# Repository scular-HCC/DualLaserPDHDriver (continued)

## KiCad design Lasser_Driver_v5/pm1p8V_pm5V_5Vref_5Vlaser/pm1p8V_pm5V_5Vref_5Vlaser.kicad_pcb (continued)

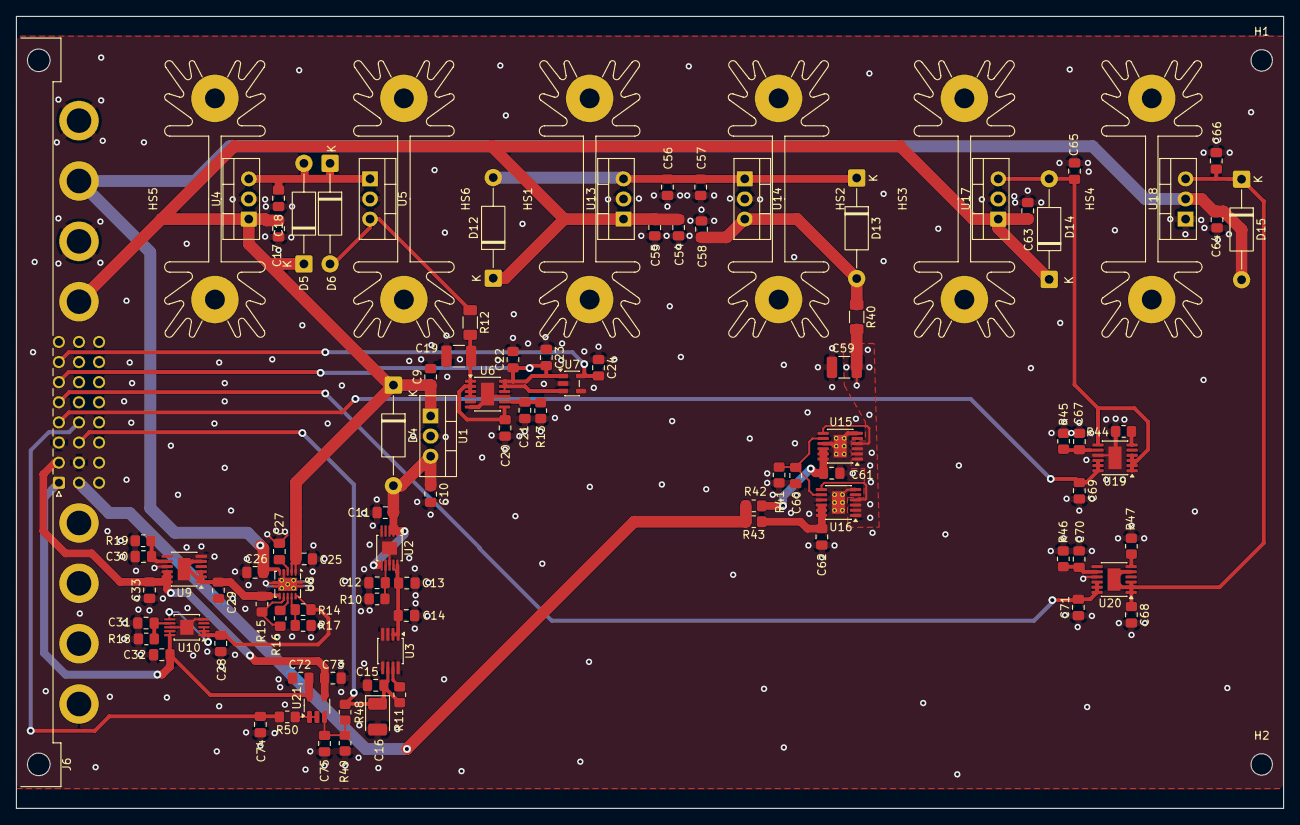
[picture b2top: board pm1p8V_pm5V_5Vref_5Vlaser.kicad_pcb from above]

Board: 2 copper layers, 160.0 x 100.0 mm, 103 parts (0 on the bottom side), 42 nets.

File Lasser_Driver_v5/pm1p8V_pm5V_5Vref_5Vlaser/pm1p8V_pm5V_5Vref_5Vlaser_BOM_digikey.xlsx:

Quantity | Manufacturer Part Number | Manufacturer | Customer Reference | Description
11 | CL21B104KBCNNNC | Samsung Electro-Mechanics | C9, C10, C14, C17, C18, C27, C55, C58, C72, C73, C74 | 100nF
12 | CL21B475KAFNNNE | Samsung Electro-Mechanics | C11, C12, C13, C20, C21, C30, C31, C54, C56, C60, C67, C70 | 4.7uF X7R
15 | C0805C106K3PACTU | KEMET | C15, C22, C25, C26, C28, C29, C32, C33, C61, C62, C65, C66, C68, C69, C71 | 10uF
1 | T520B106M016ATE100 | KEMET | C16 | 10uF 16V Polymer
1 | TMK325ABJ476MM-P | Taiyo Yuden | C19 | 47uF RC
3 | C0805C105K5RACTU | KEMET | C23, C24, C75 | 1uF
3 | CL21B334KBFNNNE | Samsung Electro-Mechanics | C57, C63, C64 | 0.33uF
1 | 1210YD107MAT2A | KYOCERA AVX | C59 | 100uF
7 | 1N4007RLG | onsemi | D4, D5, D6, D12, D13, D14, D15 | 1N4007
1 | 374144-E | TE Connectivity | J6 | DIN41612_M_3x8+8_Power_Male
1 | ERA-6AEB6042V | Panasonic Industry | R10 | 60.4k 0.1%
1 | CRCW08051K00FKEA | Vishay Dale | R17 | 1k
1 | RC1206FR-074R7L | YAGEO | R12 | 4.7R
1 | ERA-6AEB3322V | Panasonic Industry | R13 | 33.2k 0.1%
1 | ERA-6AEB1272V | Panasonic Industry | R14 | 12.7k 0.1%
2 | ERA-6AEB1433V | Panasonic Industry | R18, R19 | 143k 0.1%
1 | RC1206FR-071RL | YAGEO | R40 | 1R RC
2 | ERA-6AEB4992V | Panasonic Industry | R45, R46 | 49.9k 0.1%
1 | RC0805FR-0716KL | YAGEO | R47 | 16k
3 | MC7808CTG | onsemi | U1, U14, U17 | MC7808CTG
2 | LT3042EMSE#PBF | Analog Devices Inc. | U2, U10 | LT3042EMSE +5.5V
1 | LTC6655BHMS8-5#PBF | Analog Devices Inc. | U3 | LTC6655BHMS8-5#PBF
2 | MC7812CTG | onsemi | U4, U13 | MC7812CTG
1 | MC7805CTG | onsemi | U5 | MC7805CTG
4 | LT3045EMSE#PBF | Analog Devices Inc. | U6, U15, U16, U19 | LT3045EMSE 5V
1 | LP5907MFX-1.8/NOPB | Texas Instruments | U7 | LP5907MFX-1.8
1 | TPS7A3901DSCR | Texas Instruments | U8 | TPS7A3901DSCR
2 | LT3094EMSE#PBF | Analog Devices Inc. | U9, U20 | LT3094EMSE -14.3V
1 | MC7906CTG | onsemi | U18 | MC7906CTG
1 | OPA192IDBVR | Texas Instruments | U21 | OPA192IDBVR
1 | RC0805JR-070RL | YAGEO | R11 | 0R
1 | ERA-6AEB1373V | Panasonic Industry | R15 | 137k 0.1%
3 | ERA-6AEB103V | Panasonic Industry | R16, R48, R49 | 10k 0.1%
1 | ERA-6AEB2492V | Panasonic Industry | R41 | 24.9k 0.1%
1 | RC0805FR-07604RL | YAGEO | R44 | 604
1 | ERJ-6ENF49R9V | Panasonic Industry | R50 | 49.9R
6 | 531102B02500G | Boyd | HS1, HS2, HS3, HS4, HS5, HS6 | Heatsink TO-220
6 | 4880G | Boyd | U4, U5, U13, U14, U17, U18 iso kits | TO-220 mount kit
2 | ERJ-6BWFR020V | Panasonic Industry | R42, R43 | 20m 1%

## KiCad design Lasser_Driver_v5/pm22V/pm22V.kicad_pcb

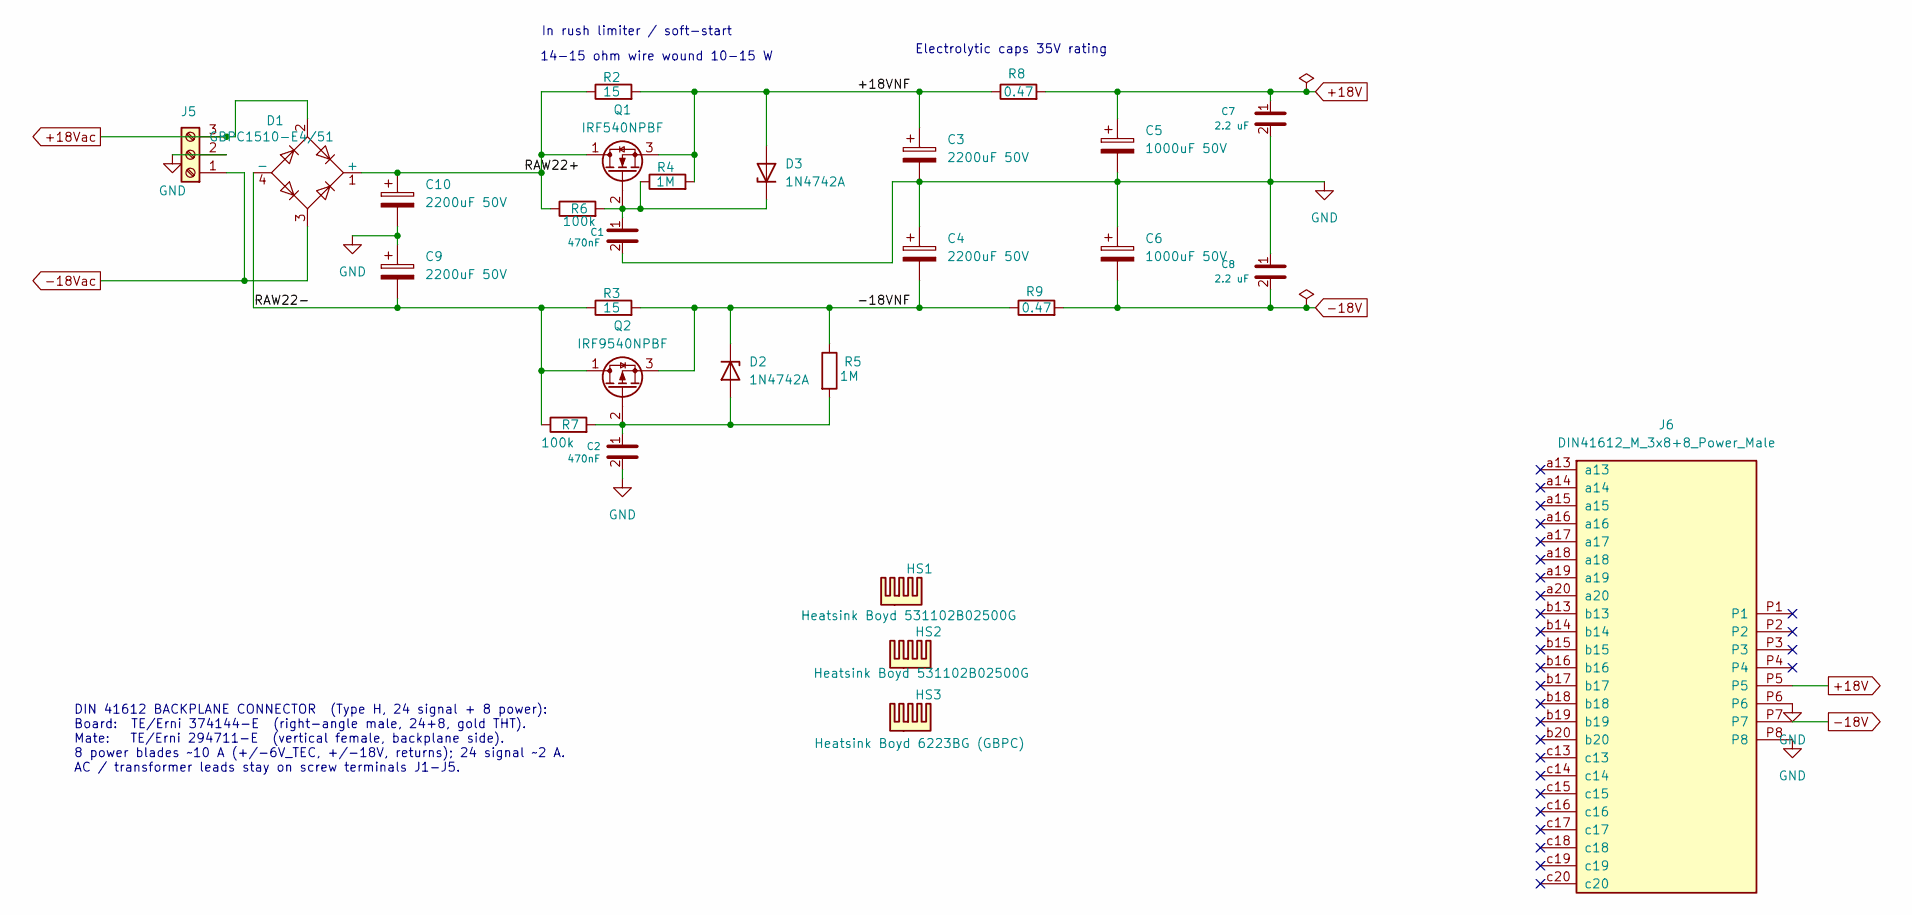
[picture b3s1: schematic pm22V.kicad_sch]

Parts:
C1, C2: 470nF; C_0805_2012Metric_Pad1.18x1.45mm_HandSolder
C3, C4, C9, C10: 2200uF 50V; CP_Radial_D18.0mm_P7.50mm
C5, C6: 1000uF 50V; CP_Radial_D16.0mm_P7.50mm
C7, C8: 2.2 uF; C_0805_2012Metric_Pad1.18x1.45mm_HandSolder
D1: GBPC1510-E4/51; Diode_Bridge_28.6x28.6x7.3mm_P18.0mm_P11.6mm
D2, D3: 1N4742A; D_DO-41_SOD81_P10.16mm_Horizontal
HS1, HS2: Heatsink Boyd 531102B02500G; Heatsink_AAVID_Extruded_531102B02500G_34.9x12.7mm_H38.1mm
HS3: Heatsink Boyd 6223BG (GBPC); Bridge_GBPC_Heatsink_Boyd_6223BG
J5: Screw_Terminal_01x03; TerminalBlock_Phoenix_MKDS-1,5-3-5.08_1x03_P5.08mm_Horizont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; MPN 1729131
J6: DIN41612_M_3x8+8_Power_Male; DIN41612_M_3x8+8_Male_Horizontal_THT_Power
Q1: IRF540NPBF; TO-220-3_Vertical
Q2: IRF9540NPBF; TO-220-3_Vertical
R2, R3: 15; R_Axial_Power_L38.0mm_W9.0mm_P45.72mm
R4, R5: 1M; R_0805_2012Metric_Pad1.20x1.40mm_HandSolder
R6, R7: 100k; R_0805_2012Metric_Pad1.20x1.40mm_HandSolder
R8, R9: 0.47; R_1206_3216Metric_Pad1.30x1.75mm_HandSolder; MPN CRL1206-FW-R470ELF

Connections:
+18V: C5.1, C7.1, J6.P5, R8.2
+18Vac: D1.2, J5.3
-18V: C6.2, C8.2, J6.P7, R9.2
-18Vac: D1.3, J5.1
/+18VNF: C3.1, D3.2 (A), Q1.3 (S), R2.2, R4.2, R8.1
/-18VNF: C4.2, D2.1 (K), Q2.3 (S), R3.2, R5.1, R9.1
/RAW22+: C10.1, D1.1 (+), Q1.1 (D), R2.1, R6.1
/RAW22-: C9.2, D1.4 (-), Q2.1 (D), R3.1, R7.1
GND: C1.2, C2.2, C3.2, C4.1, C5.2, C6.1, C7.2, C8.1, C9.1, C10.2, J5.2, J6.P6, J6.P8
unnamed: C2.1, D2.2 (A), Q2.2 (G), R5.2, R7.2
unnamed: C1.1, D3.1 (K), Q1.2 (G), R4.1, R6.2

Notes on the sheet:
Electrolytic caps 35V rating
DIN 41612 BACKPLANE CONNECTOR (Type H, 24 signal + 8 power): Board: TE/Erni 374144-E (right-angle male, 24+8, gold THT). Mate: TE/Erni 294711-E (vertical female, backplane side). 8 power blades ~10 A (+/-6V_TEC, +/-18V, returns); 24 signal ~2 A. AC / transformer leads stay on screw terminals J1-J5.
In rush limiter / soft-start
14-15 ohm wire wound 10-15 W

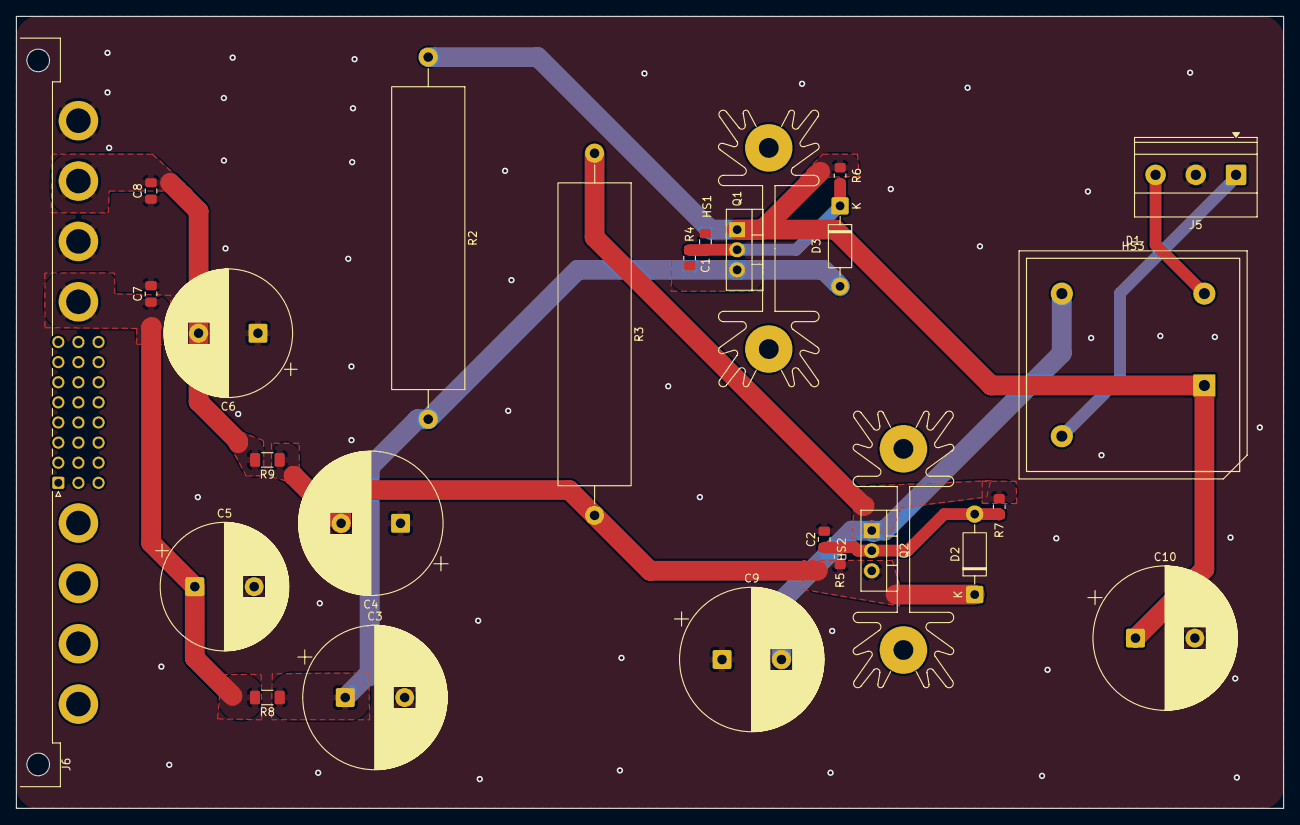
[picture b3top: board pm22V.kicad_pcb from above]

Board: 2 copper layers, 160.0 x 100.0 mm, 28 parts (0 on the bottom side), 11 nets.

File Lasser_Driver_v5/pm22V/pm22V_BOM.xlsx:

Quantity | Manufacturer Part Number | Manufacturer | Digi-Key Part Number | Customer Reference | Description | Mount | Notes
2 | CL21B474KBFNNNE | Samsung Electro-Mechanics | 1276-1039-2-ND | C1, C2 | CAP CER 0.47uF 50V X7R 0805 | SMD
2 | EEU-FC1H222 | Panasonic | P10335-ND | C3, C4 | CAP ALUM 2200uF 50V 20% RADIAL 18mm P7.5 | THT
2 | EEU-FC1H102 | Panasonic | P10333-ND | C5, C6 | CAP ALUM 1000uF 50V 20% RADIAL 16mm P7.5 | THT
2 | 08055C225KAT2A | KYOCERA AVX | 478-KGM21AR71H225KUTR-ND | C7, C8 | CAP CER 2.2uF 50V X7R 0805 | SMD
1 | GBPC1510-E4/51 | Vishay General Semiconductor | GBPC1510-E4/51-ND | D1 | BRIDGE RECT 1PH 1kV 15A GBPC | THT | Bolts to HS3
2 | 1N4742ATR | onsemi | 1N4742AFSTR-ND | D2, D3 | DIODE ZENER 12V 1W DO-41 | THT | gate Vgs clamp
2 | 531102B02500G | Boyd (Aavid) | HS352-ND | HS1, HS2 | HEATSINK TO-220 W/PINS 1.5in | Mech | Off-board / on Q1,Q2 tab
1 | 6223BG | Boyd (Aavid) | 6223BG-ND | HS3 | HEATSINK BRIDGE RECTIFIER 0.163in | Mech | Off-board / bolts to D1
1 | 1757255 | Phoenix Contact | 277-1107-ND | J5 | TERM BLOCK HDR 3POS 5.08mm (MSTBA 2,5/3-G-5,08) | THT | Transformer leads in
1 | 374144-E | ERNI / TE Connectivity | 2684-374144-E-ND | J6 | CONN DIN41612 TYPE M 32POS R/A MALE (24 sig+8 pwr) | THT | ** STOCK 0 - backorder / verify exact Type-M part **
1 | IRF540NPBF | Infineon Technologies | IRF540NPBF-ND | Q1 | MOSFET N-CH 100V 33A TO-220 | THT | + rail pass FET; on HS1
1 | IRF9540NPBF | Infineon Technologies | IRF9540NPBF-ND | Q2 | MOSFET P-CH 100V 23A TO-220 | THT | - rail pass FET; on HS2
2 | SQPW1015RJ | TE Connectivity | A137409-ND | R2, R3 | RES 15 OHM 5% 10W AXIAL | THT | Soft-start / inrush
2 | RC0805FR-071ML | Yageo | 311-1.00MCRTR-ND | R4, R5 | RES 1M OHM 1% 1/8W 0805 | SMD | gate bleed
2 | RC0805FR-07100KL | Yageo | 311-100KCRTR-ND | R6, R7 | RES 100k OHM 1% 1/8W 0805 | SMD | gate pull from RAW
2 | CRL1206-FW-R470ELF | Bourns | 118-CRL1206-FW-R470ELFTR-ND | R8, R9 | RES 0.47 OHM 1% 1/2W 1206 | SMD | output damping
1 | VPT36-1390 | Triad Magnetics | 237-1334-ND | T1 | XFMR TOROIDAL 50VA 115/230V > 2x18V CHASSIS | Mech | Off-board / chassis mount

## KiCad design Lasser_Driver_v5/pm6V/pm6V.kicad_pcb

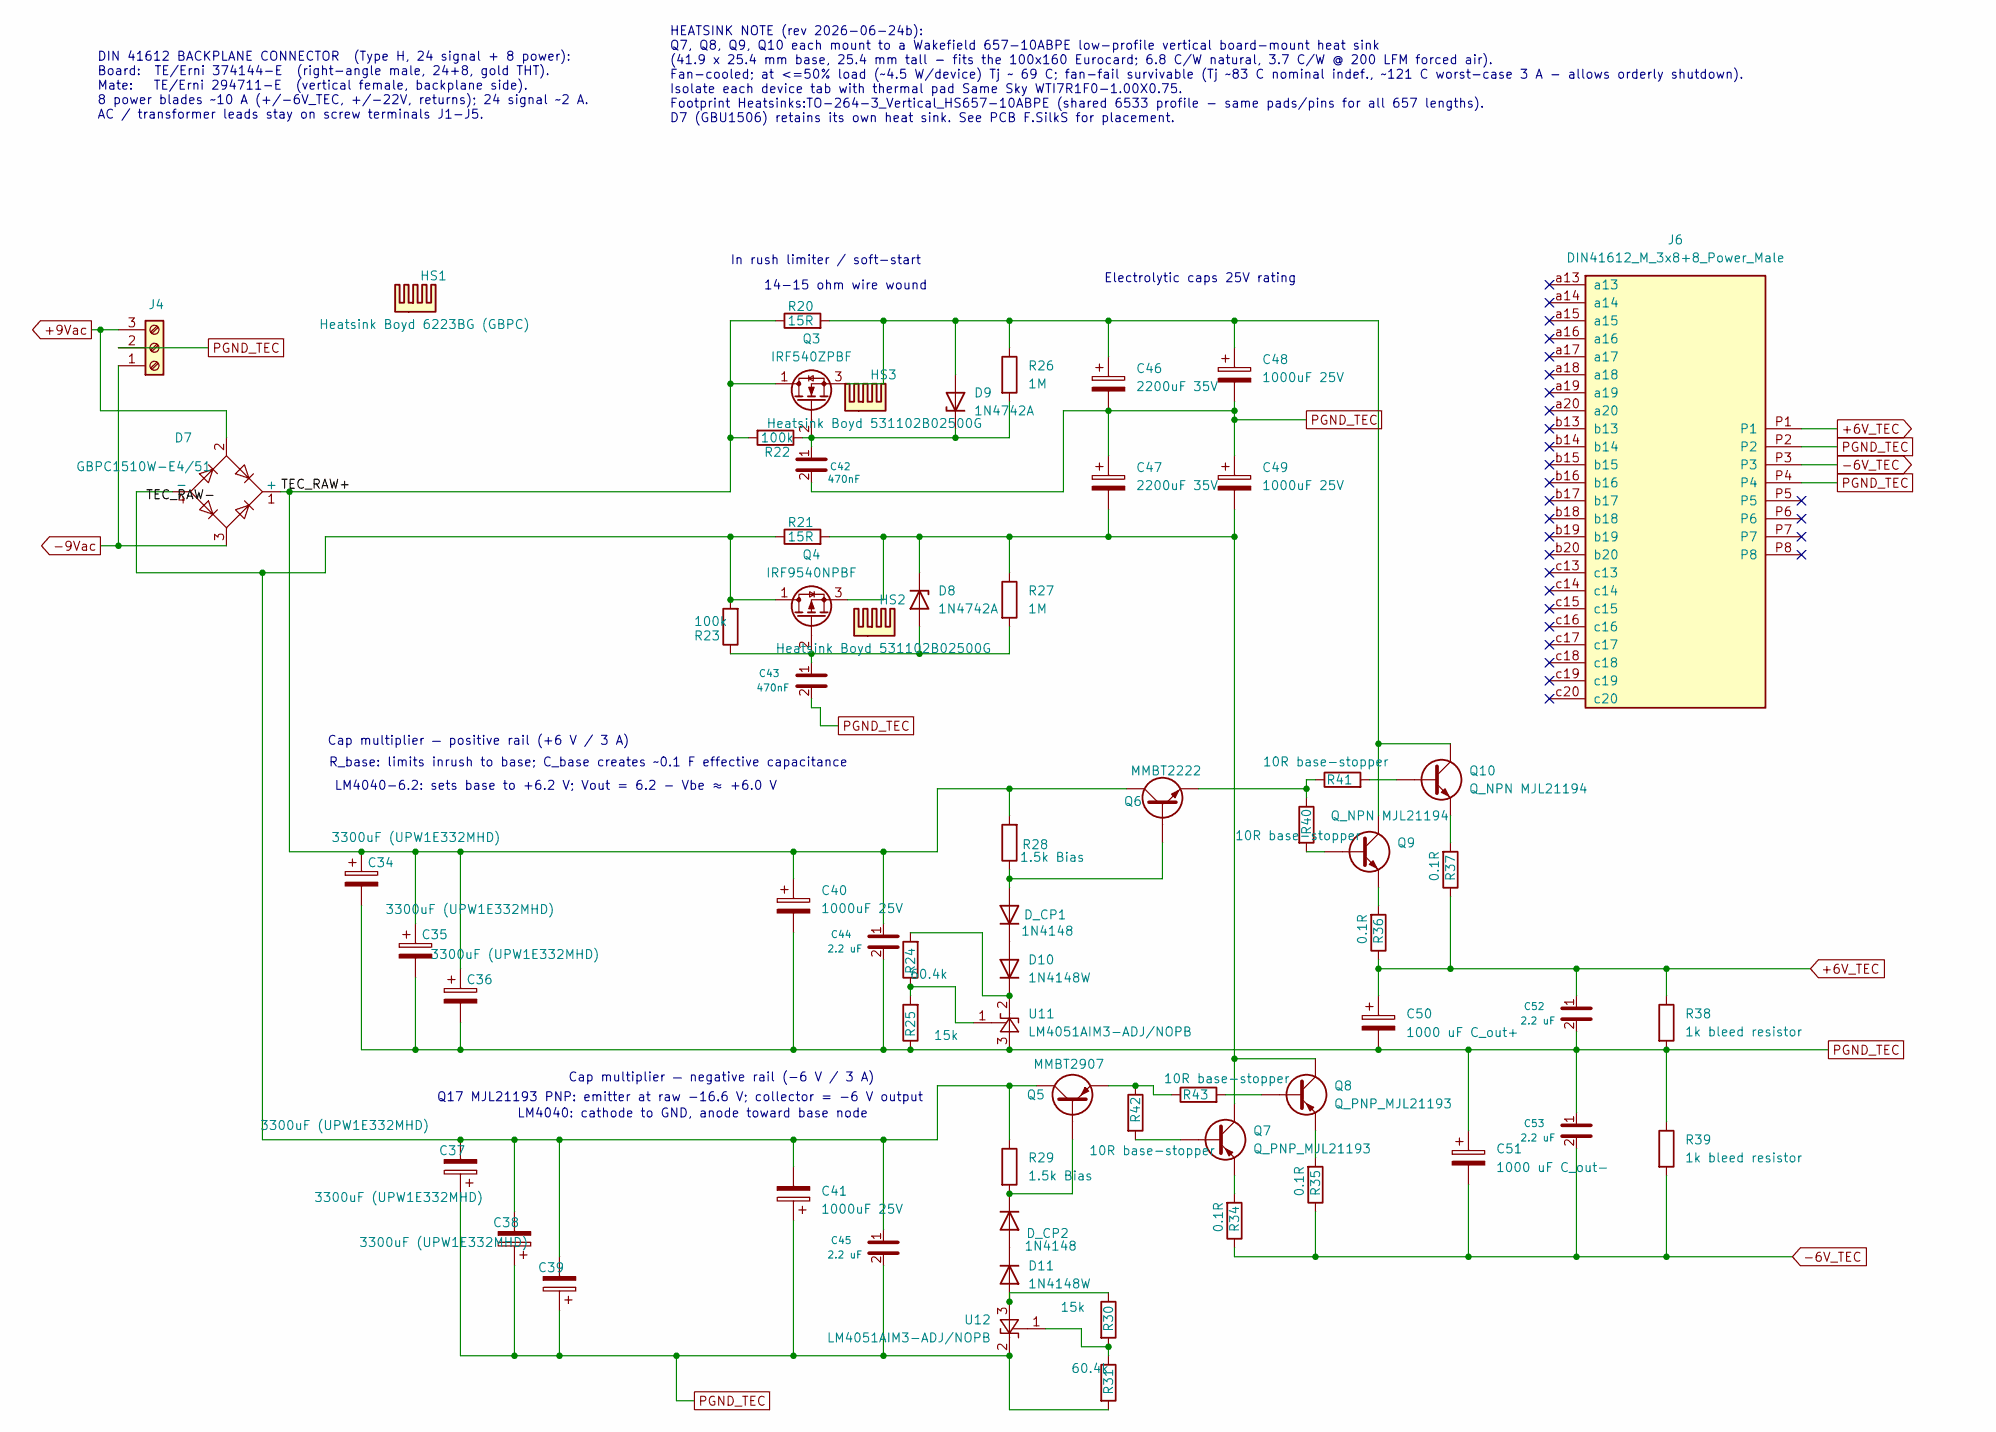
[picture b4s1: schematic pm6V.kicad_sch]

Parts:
C34, C35, C36, C37, C38, C39: 3300uF (UPW1E332MHD); CP_Radial_D16.0mm_P7.50mm; Manufacturer Part Number UHE1E332MHD; DigiKey P/N 493-1568-ND
C40, C41, C48, C49: 1000uF 25V; CP_Radial_D12.5mm_P5.00mm; Manufacturer Part Number UHE1E102MPD; DigiKey P/N 493-1557-ND
C42, C43: 470nF; C_0805_2012Metric_Pad1.18x1.45mm_HandSolder; Manufacturer Part Number CL21B474KBFNNNE; DigiKey P/N 1276-1039-2-ND
C44, C45, C52, C53: 2.2 uF; C_0805_2012Metric_Pad1.18x1.45mm_HandSolder; Manufacturer Part Number CL21B225KBYNNWE; DigiKey P/N 1276-CL21B225KBYNNWETR-ND
C46, C47: 2200uF 35V; CP_Radial_D18.0mm_P7.50mm; Manufacturer Part Number UVZ1H222MHD; DigiKey P/N 493-1346-ND
C50: 1000 uF C_out+; CP_Radial_D12.5mm_P5.00mm; Manufacturer Part Number UHE1E102MPD; DigiKey P/N 493-1557-ND
C51: 1000 uF C_out-; CP_Radial_D12.5mm_P5.00mm; Manufacturer Part Number UHE1E102MPD; DigiKey P/N 493-1557-ND
D7: GBPC1510W-E4/51; Diode_Bridge_28.6x28.6x7.3mm_P18.0mm_P11.6mm; Manufacturer Part Number GBPC1510W; DigiKey P/N 2616-GBPC1510W-ND
D8, D9: 1N4742A; D_DO-41_SOD81_P10.16mm_Horizontal; Manufacturer Part Number 1N4742ATR; DigiKey P/N 1N4742AFSTR-ND
D10, D11: 1N4148W; D_SOD-123; Manufacturer Part Number 1N4148W-7-F; DigiKey P/N 1N4148W-FDITR-ND
D_CP1, D_CP2: 1N4148; D_SOD-123; Manufacturer Part Number 1N4148W-7-F; DigiKey P/N 1N4148W-FDITR-ND
HS1: Heatsink Boyd 6223BG (GBPC); Bridge_GBPC_Heatsink_Boyd_6223BG; Manufacturer Part Number 6223BG; DigiKey P/N 6223BG-ND
HS2, HS3: Heatsink Boyd 531102B02500G; Heatsink_AAVID_Extruded_531102B02500G_34.9x12.7mm_H38.1mm; Manufacturer Part Number 531102B02500G; DigiKey P/N HS352-ND
J4: Screw_Terminal_01x03; TerminalBlock_Phoenix_MKDS-1,5-3-5.08_1x03_P5.08mm_Horizont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; Manufacturer Part Number 1729131; DigiKey P/N 277-1248-ND
J6: DIN41612_M_3x8+8_Power_Male; DIN41612_M_3x8+8_Male_Horizontal_THT_Power; Manufacturer Part Number 374144-E; DigiKey P/N 2684-374144-E-ND
Q3: IRF540ZPBF; TO-220-3_Vertical; Manufacturer Part Number IRF540ZPBF; DigiKey P/N IRF540ZPBF-ND
Q4: IRF9540NPBF; TO-220-3_Vertical; Manufacturer Part Number IRF9540NPBF; DigiKey P/N IRF9540NPBF-ND
Q5: MMBT2907; SOT-23_Handsoldering; Manufacturer Part Number MMBT2907A-TP; DigiKey P/N MMBT2907A-TPMSTR-ND
Q6: MMBT2222; SOT-23_Handsoldering; Manufacturer Part Number MMBT2222ALT1G; DigiKey P/N MMBT2222ALT1GOSTR-ND
Q7, Q8: Q_PNP_MJL21193; TO-264-3_Vertical_HS657-10ABPE; Manufacturer Part Number MJL21193G; DigiKey P/N MJL21193GOS-ND
Q9, Q10: Q_NPN MJL21194; TO-264-3_Vertical_HS657-10ABPE; Manufacturer Part Number MJL21194G; DigiKey P/N MJL21194GOS-ND
R20, R21: 15R; R_Axial_Power_L38.0mm_W9.0mm_P45.72mm; Manufacturer Part Number TUW15J15RE; DigiKey P/N TUW15J15RE-ND
R22, R23: 100k; R_0805_2012Metric_Pad1.20x1.40mm_HandSolder; Manufacturer Part Number RC0805FR-07100KL; DigiKey P/N 311-100KCRTR-ND
R24, R31: 60.4k; R_0805_2012Metric_Pad1.20x1.40mm_HandSolder; Manufacturer Part Number ERJ-6ENF6042V; DigiKey P/N P60.4KCTR-ND
R25, R30: 15k; R_0805_2012Metric_Pad1.20x1.40mm_HandSolder; Manufacturer Part Number RC0805FR-0715KL; DigiKey P/N 311-15.0KCRTR-ND
R26, R27: 1M; R_0805_2012Metric_Pad1.20x1.40mm_HandSolder; Manufacturer Part Number RC0805FR-071ML; DigiKey P/N 311-1.00MCRTR-ND
R28, R29: 1.5k Bias; R_0805_2012Metric_Pad1.20x1.40mm_HandSolder; Manufacturer Part Number RC0805FR-071K5L; DigiKey P/N 311-1.50KCRTR-ND
R34, R35, R36, R37: 0.1R; R_2512_6332Metric_Pad1.40x3.35mm_HandSolder; Manufacturer Part Number WSL2512R1000FEA; DigiKey P/N WSLG-.10TR-ND
R38, R39: 1k bleed resistor; R_0805_2012Metric_Pad1.20x1.40mm_HandSolder; Manufacturer Part Number CRCW08051K00FKEA; DigiKey P/N 541-1.00KCTR-ND
R40, R41, R42, R43: 10R base-stopper; R_0805_2012Metric_Pad1.20x1.40mm_HandSolder; Manufacturer Part Number RC0805FR-0710RL; DigiKey P/N 311-10.0CRTR-ND
U11, U12: LM4051AIM3-ADJ/NOPB; SOT-23_Handsoldering; Manufacturer Part Number LM4051AIM3-ADJ/NOPB; DigiKey P/N LM4051AIM3-ADJ/NOPBTR-ND

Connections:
+6V_TEC: C50.1, C52.1, J6.P1, R36.1, R37.1, R38.1
+9Vac: D7.2, J4.3
-6V_TEC: C51.2, C53.2, J6.P3, R34.1, R35.1, R39.2
-9Vac: D7.3, J4.1
/TEC_RAW+: C34.1, C35.1, C36.1, C40.1, C44.1, D7.1 (+), Q3.1 (D), Q6.3 (C), R20.1, R22.2, R28.2
/TEC_RAW-: C37.2, C38.2, C39.2, C41.2, C45.1, D7.4 (-), Q4.1 (D), Q5.3 (C), R21.1, R23.2, R29.1
unnamed: C43.1, D8.2 (A), Q4.2 (G), R23.1, R27.2
unnamed: C47.2, C49.2, D8.1 (K), Q4.3 (S), Q7.2 (C), Q8.2 (C), R21.2, R27.1
unnamed: C46.1, C48.1, D9.2 (A), Q3.3 (S), Q9.2 (C), Q10.2 (C), R20.2, R26.1
unnamed: C42.1, D9.1 (K), Q3.2 (G), R22.1, R26.2
unnamed: D10.2 (A), D_CP1.1 (K)
unnamed: D10.1 (K), R24.2, U11.2 (K)
unnamed: D11.2 (A), R30.1, U12.3 (A)
unnamed: D11.1 (K), D_CP2.2 (A)
unnamed: D_CP1.2 (A), Q6.1 (B), R28.1
unnamed: D_CP2.1 (K), Q5.1 (B), R29.2
unnamed: Q5.2 (E), R42.1, R43.1
unnamed: Q6.2 (E), R40.1, R41.1
unnamed: Q7.1 (B), R42.2
unnamed: Q7.3 (E), R34.2
unnamed: Q8.1 (B), R43.2
unnamed: Q8.3 (E), R35.2
unnamed: Q9.1 (B), R40.2
unnamed: Q9.3 (E), R36.2
unnamed: Q10.1 (B), R41.2
unnamed: Q10.3 (E), R37.2
unnamed: R24.1, R25.2, U11.1 (FB)
unnamed: R30.2, R31.1, U12.1 (FB)
PGND_TEC: C34.2, C35.2, C36.2, C37.1, C38.1, C39.1, C40.2, C41.1, C42.2, C43.2, C44.2, C45.2, C46.2, C47.1, C48.2, C49.1, C50.2, C51.1, C52.2, C53.1, J4.2, J6.P2, J6.P4, R25.1, R31.2, R38.2, R39.1, U11.3 (A), U12.2 (K)

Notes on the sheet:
Cap multiplier — negative rail (-6 V / 3 A)
Cap multiplier — positive rail (+6 V / 3 A)
LM4040: cathode to GND, anode toward base node
R_base: limits inrush to base; C_base creates ~0.1 F effective capacitance
14-15 ohm wire wound
In rush limiter / soft-start
DIN 41612 BACKPLANE CONNECTOR (Type H, 24 signal + 8 power): Board: TE/Erni 374144-E (right-angle male, 24+8, gold THT). Mate: TE/Erni 294711-E (vertical female, backplane side). 8 power blades ~10 A (+/-6V_TEC, +/-22V, returns); 24 signal ~2 A. AC / transformer leads stay on screw terminals J1-J5.
Q17 MJL21193 PNP: emitter at raw -16.6 V; collector = -6 V output
HEATSINK NOTE (rev 2026-06-24b): Q7, Q8, Q9, Q10 each mount to a Wakefield 657-10ABPE low-profile vertical board-mount heat sink (41.9 x 25.4 mm base, 25.4 mm tall - fits the 100x160 Eurocard; 6.8 C/W natural, 3.7 C/W @ 200 LFM forced air). Fan-cooled; at <=50% load (~4.5 W/device) Tj ~ 69 C; fan-f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
Electrolytic caps 25V rating
LM4040-6.2: sets base to +6.2 V; Vout = 6.2 - Vbe ≈ +6.0 V

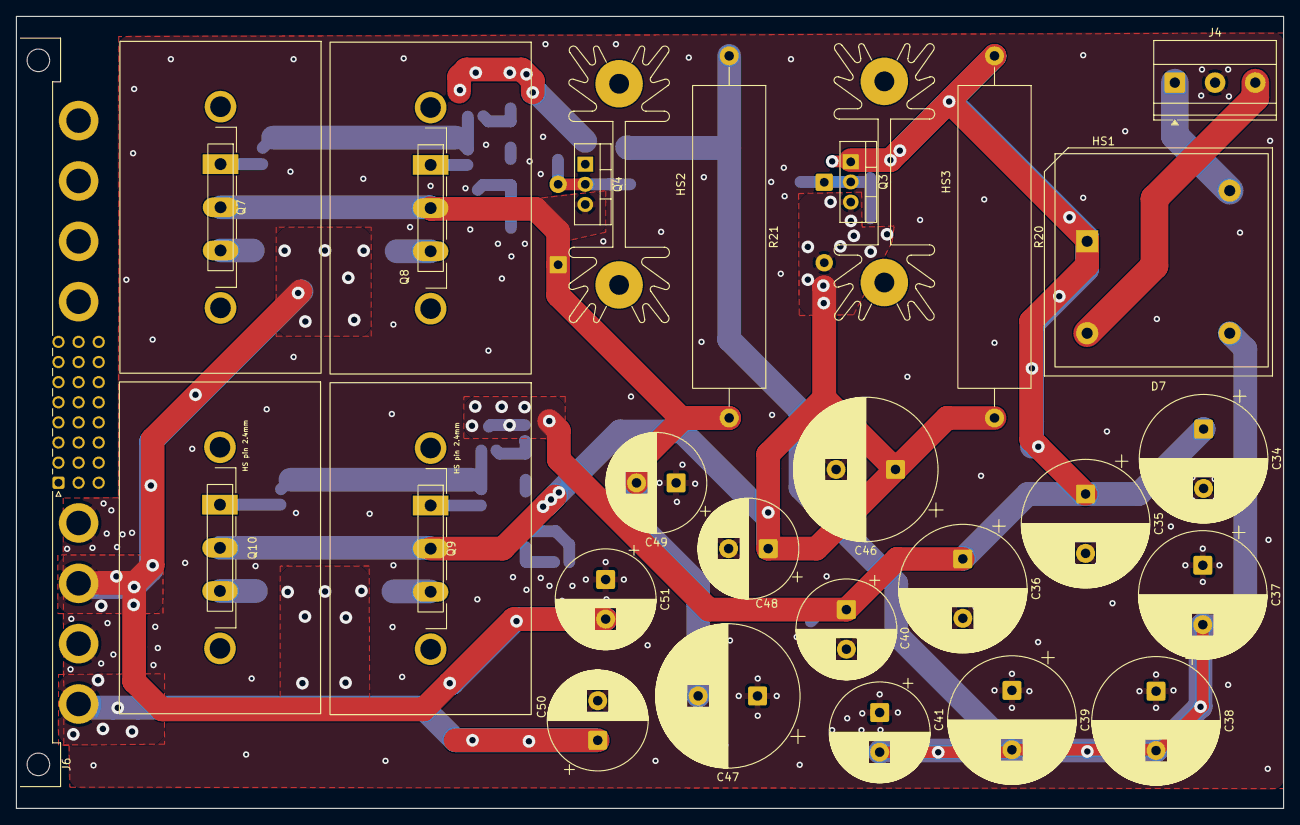
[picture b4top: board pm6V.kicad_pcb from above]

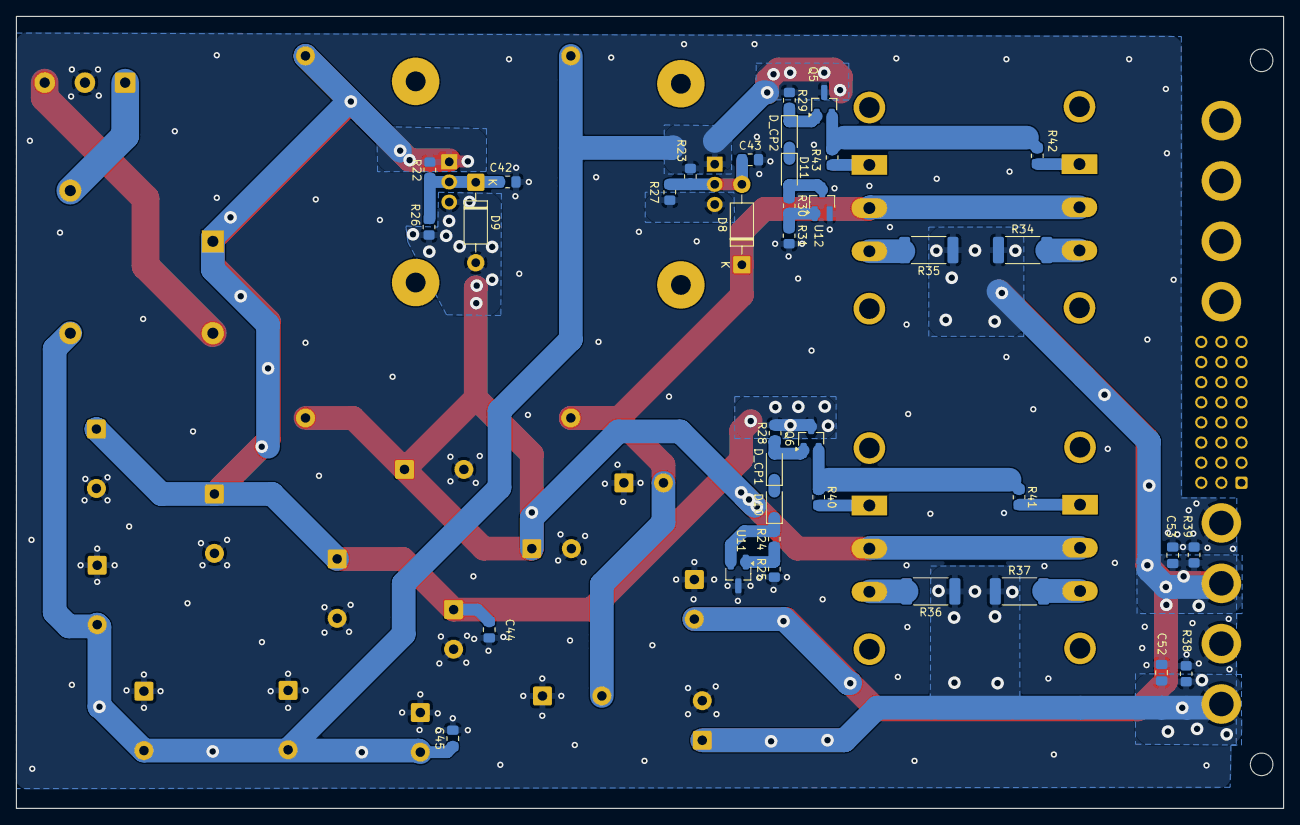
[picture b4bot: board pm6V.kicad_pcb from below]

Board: 2 copper layers, 160.0 x 100.0 mm, 64 parts (36 on the bottom side), 29 nets.
